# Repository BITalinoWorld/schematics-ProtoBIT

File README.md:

# ProtoBIT

Schematics and physical drawings for the ProtoBIT board, which
includes the UC-E6 and Molex Sherlock connectors footprint and pin
breakout. Source files (.brd & .sch) can be opened with CadSoft's EAGLE PCB design software: https://cadsoft.io

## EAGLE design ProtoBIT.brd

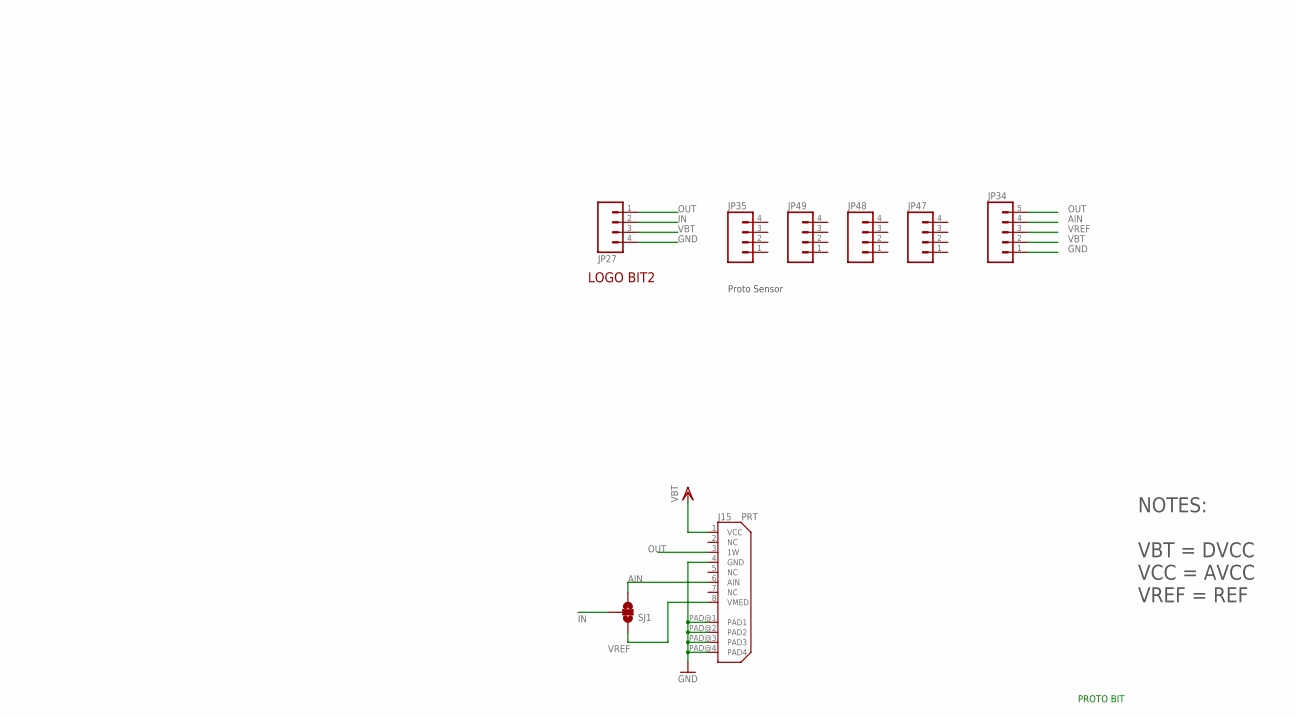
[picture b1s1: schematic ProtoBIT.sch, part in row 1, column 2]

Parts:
J15: PRT; 8PIN_MINI_USB_SINGLE_ROW_SMD
JP27: M04JST-PTH; JST-4-PTH
JP34: M05; JST-5-PTH-NO_SILK
JP35, JP47, JP48, JP49: M04PTH; 1X04
SJ1: SOLDERJUMPER_2WAYS; SJ_3
U$14: LOGO_BIT2(4.72X3.78); LOGO_BIT2

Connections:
AIN: J15.6 (AIN), JP34.4, SJ1.3
GND: J15.4 (GND), J15.PAD@1 (PAD1), J15.PAD@2 (PAD2), J15.PAD@3 (PAD3), J15.PAD@4 (PAD4), JP27.4, JP34.1
IN: JP27.2, SJ1.2
OUT: J15.3 (1W), JP27.1, JP34.5
VBT: J15.1 (VCC), JP27.3, JP34.2
VREF: J15.8 (VMED), JP34.3, SJ1.1

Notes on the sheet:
PROTO BIT
Proto Sensor
NOTES: VBT = DVCC VCC = AVCC VREF = REF

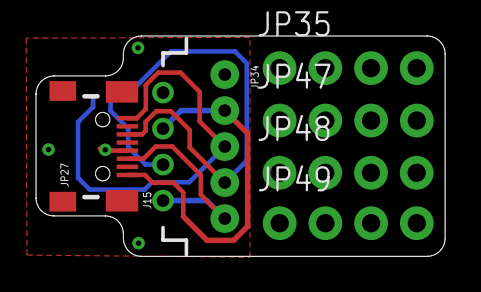
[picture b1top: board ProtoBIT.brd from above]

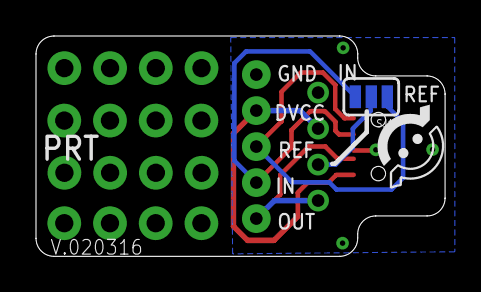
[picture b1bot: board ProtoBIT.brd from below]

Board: 2 copper layers, 22.7 x 12.2 mm, 9 parts (2 on the bottom side), 6 nets.

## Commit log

2019-02-27 repo creation
2019-02-27 added schematics

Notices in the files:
parts and their libraries:
SparkFun: Licensing: CC v3.0 Share-Alike You are welcome to use this library for commercial purposes.
SparkFun-Retired: Licensing:Creative Commons ShareAlike 4.0 International - https://creativecommons.org/licenses/by-sa/4.0
